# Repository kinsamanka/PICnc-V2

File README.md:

PICnc-V2
========

PICnc V2 is a PIC32 based hardware step generator board that is designed for MachineKit

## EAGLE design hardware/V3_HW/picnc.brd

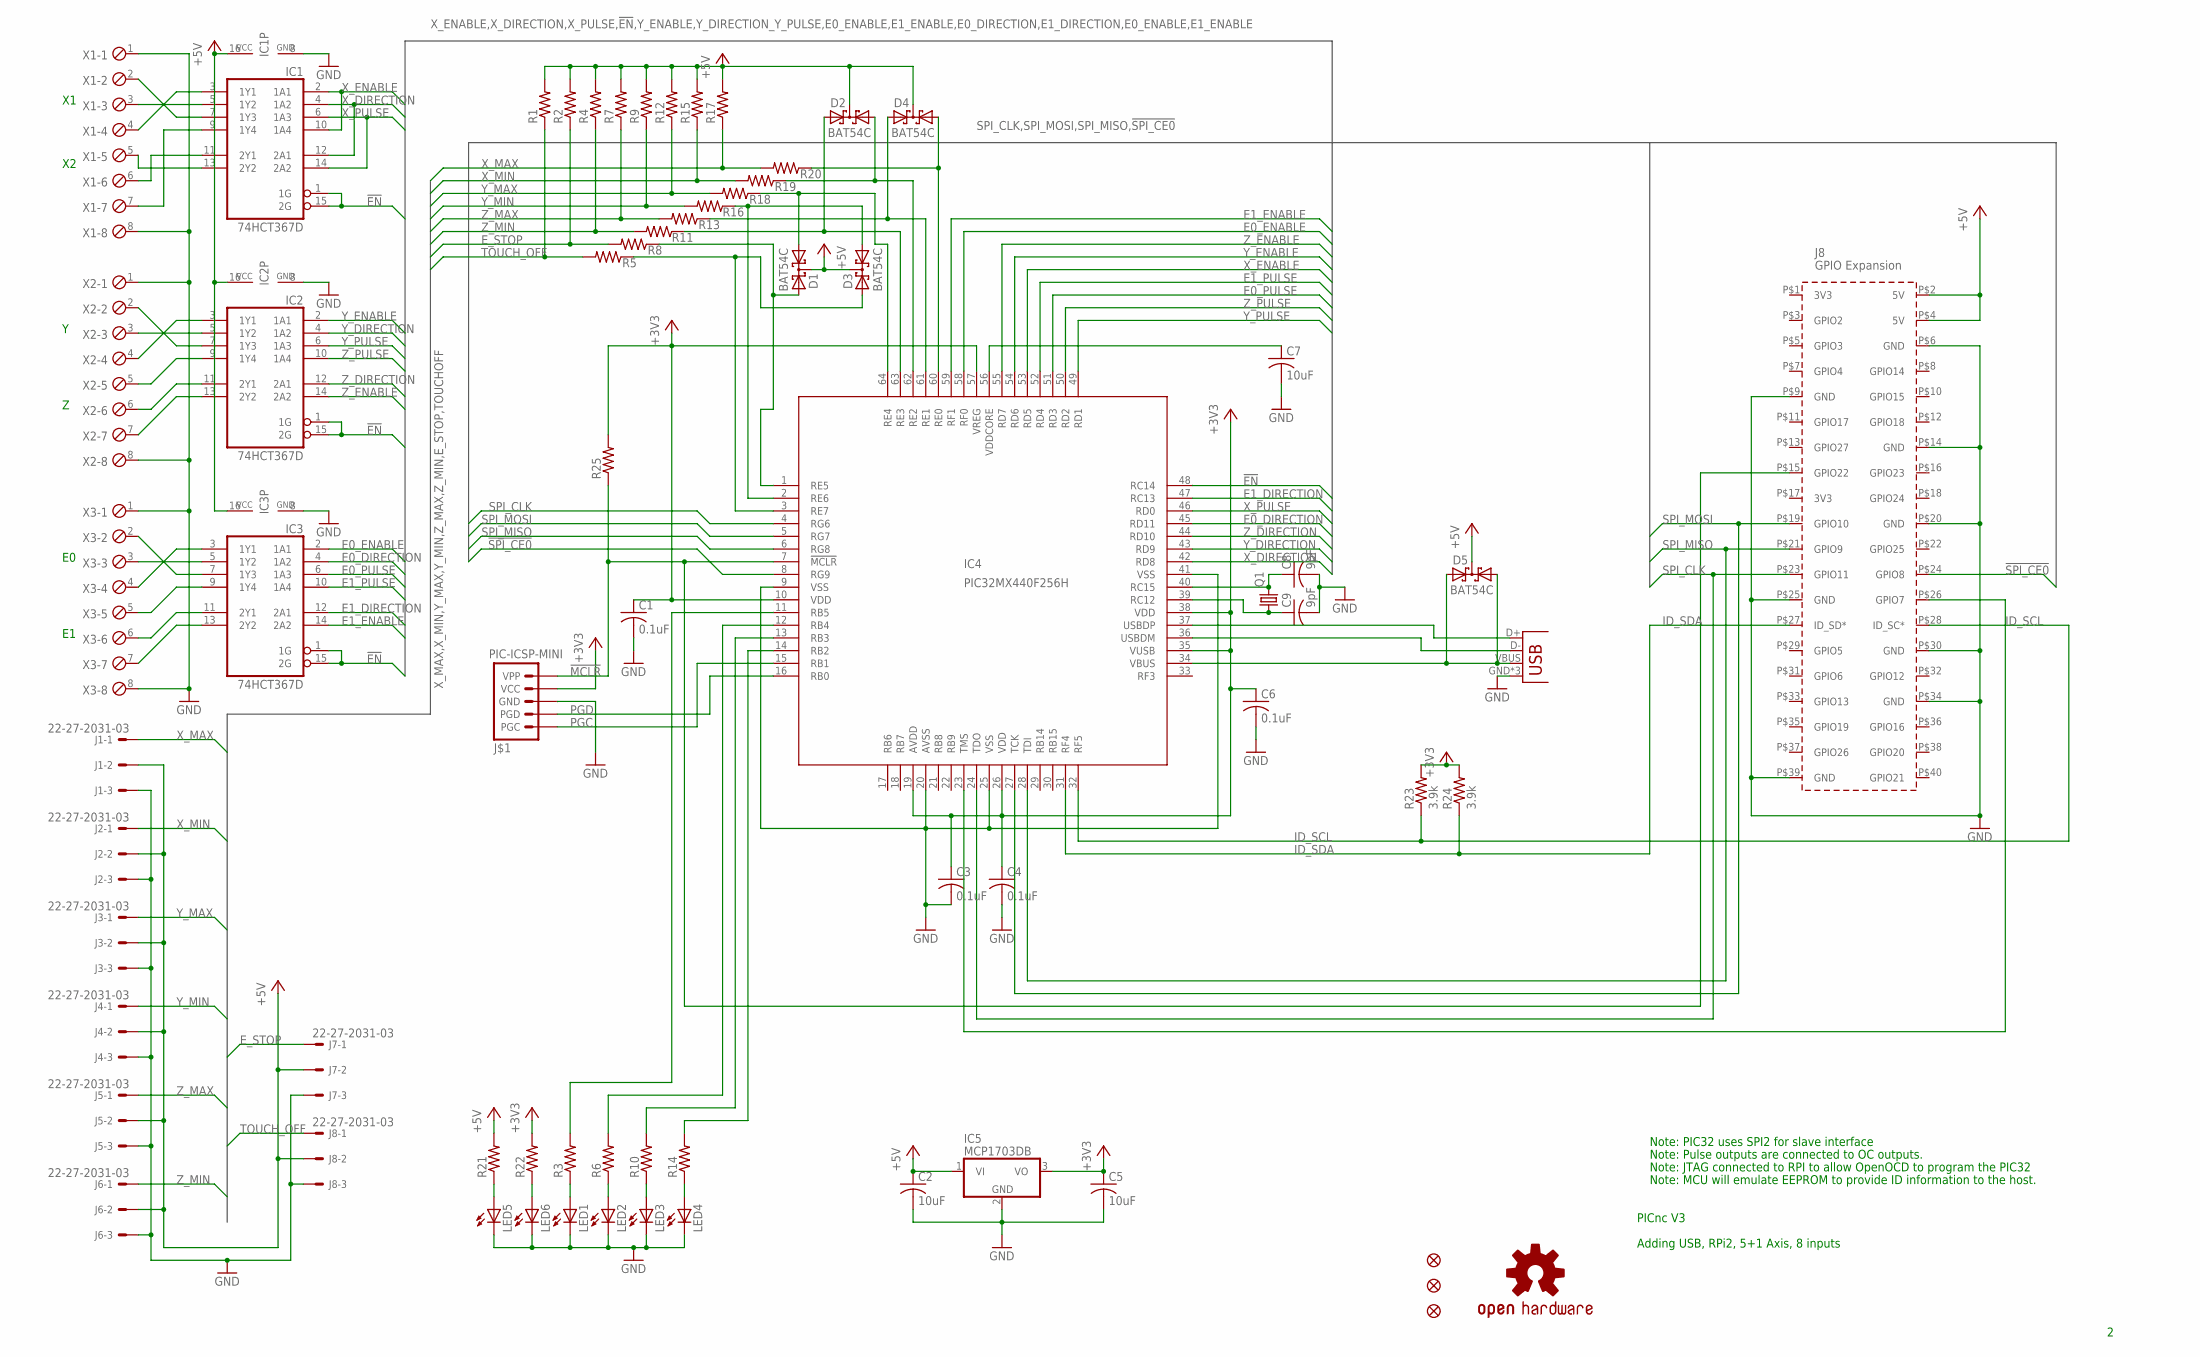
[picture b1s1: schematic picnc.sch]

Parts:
C1, C3, C4, C6: 0.1uF; C0603
C2, C5, C7: 10uF; C1206
C8, C9: 9pF; C0603
D1, D2, D3, D4, D5: BAT54C; SOT23
FID1, FID2, FID3: FIDUCIAL1.5X3; FIDUCIAL-1.5X3
IC1, IC2, IC3: 74HCT367D; SO16
IC4: PIC32MX440F256H; TQFP64-10X10
IC5: MCP1703DB; SOT223
J1, J2, J3, J4, J5, J6, J7, J8: 22-27-2031-03; 6410-03
J9: RPI2_HAT
J$1: PIC-ICSP-MINI
JP1: USB-MICROB
LED1, LED2, LED3, LED4, LED5, LED6: LEDCHIP-LED0603; CHIP-LED0603
LOGO1: OSHW-LOGOS; OSHW-LOGO-S
Q1: CTS406C35D08M00000; CTS406
R1, R2, R3, R4, R5, R6, R7, R8, R9, R10, R11, R12, R13, R14, R15, R16, R17, R18, R19, R20, R21, R22, R25: R-US_R0603; R0603
R23, R24: 3.9k; R0603
X1, X2, X3: MPT8; 8POL254

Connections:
!EN: IC1.1 (1G), IC1.15 (2G), IC2.1 (1G), IC2.15 (2G), IC3.1 (1G), IC3.15 (2G), IC4.48 (RC14)
!MCLR: IC4.7 (!MCLR), J9.P$15 (GPIO22), J$1.1 (VPP), R25.1
!SPI_CE0: J9.P$24 (GPIO8)
+3V3: C1.1, C3.1, C4.1, C5.1, C6.1, IC4.10 (VDD), IC4.19 (AVDD), IC4.26 (VDD), IC4.35 (VUSB), IC4.38 (VDD), IC4.57 (VREG), IC5.3 (VO), J$1.2 (VCC), R22.2, R23.2, R24.2, R25.2
+5V: C2.1, D1.3 (CC), D2.3 (CC), D3.3 (CC), D4.3 (CC), D5.3 (CC), IC1.16 (VCC), IC2.16 (VCC), IC3.16 (VCC), IC5.1 (VI), J1.2, J2.2, J3.2, J4.2, J5.2, J6.2, J7.2, J8.2, J9.P$2 (5V), J9.P$4 (5V), R1.2, R2.2, R4.2, R7.2, R9.2, R12.2, R15.2, R17.2, R21.2
D_N: IC4.36 (USBDM), JP1.D-
D_P: IC4.37 (USBDP), JP1.D+
E0_DIRECTION: IC3.4 (1A2), IC4.45 (RD11)
E0_ENABLE: IC3.2 (1A1), IC4.58 (RF0)
E0_PULSE: IC3.6 (1A3), IC4.51 (RD3)
E1_DIRECTION: IC3.12 (2A1), IC4.47 (RC13)
E1_ENABLE: IC3.14 (2A2), IC4.59 (RF1)
E1_PULSE: IC3.10 (1A4), IC4.52 (RD4)
E_STOP: J7.1, R2.1, R8.2
GND: C1.2, C2.2, C3.2, C4.2, C5.2, C6.2, C7.2, C8.2, C9.2, IC1.8 (GND), IC2.8 (GND), IC3.8 (GND), IC4.9 (VSS), IC4.20 (AVSS), IC4.25 (VSS), IC4.41 (VSS), IC5.2 (GND), J1.3, J2.3, J3.3, J4.3, J5.3, J6.3, J7.3, J8.3, J9.P$6 (GND), J9.P$9 (GND), J9.P$14 (GND), J9.P$20 (GND), J9.P$25 (GND), J9.P$30 (GND), J9.P$34 (GND), J9.P$39 (GND), J$1.3 (GND), JP1.GND, JP1.MT1 (GND), JP1.MT2 (GND), LED1.C, LED2.C, LED3.C, LED4.C, LED5.C, LED6.C, X1.1, X1.8, X2.1, X2.8, X3.1, X3.8
ID_SCL: IC4.32 (RF5), J9.P$28 (ID_SC*), R23.1
ID_SDA: IC4.31 (RF4), J9.P$27 (ID_SD*), R24.1
unnamed: IC1.7 (1Y3), X1.2
unnamed: IC1.3 (1Y1), X1.4
unnamed: IC1.5 (1Y2), X1.3
unnamed: IC1.9 (1Y4), X1.7
unnamed: IC1.11 (2Y1), X1.6
unnamed: IC1.13 (2Y2), X1.5
unnamed: C8.1, IC4.40 (RC15), Q1.3 (2)
unnamed: IC2.5 (1Y2), X2.3
unnamed: C7.1, IC4.56 (VDDCORE)
unnamed: IC2.3 (1Y1), X2.4
unnamed: IC2.7 (1Y3), X2.2
unnamed: IC2.9 (1Y4), X2.5
unnamed: IC2.11 (2Y1), X2.6
unnamed: IC2.13 (2Y2), X2.7
unnamed: IC3.7 (1Y3), X3.2
unnamed: IC3.5 (1Y2), X3.3
unnamed: IC3.3 (1Y1), X3.4
unnamed: IC3.9 (1Y4), X3.5
unnamed: IC3.11 (2Y1), X3.6
unnamed: IC3.13 (2Y2), X3.7
unnamed: C9.1, IC4.39 (RC12), Q1.1
unnamed: LED1.A, R3.1
unnamed: LED2.A, R6.1
unnamed: LED3.A, R10.1
unnamed: LED4.A, R14.1
unnamed: D3.2 (A2), IC4.3 (RE7), R5.1
unnamed: IC4.14 (RB2), R14.2
unnamed: IC4.13 (RB3), R10.2
unnamed: IC4.12 (RB4), R6.2
unnamed: IC4.11 (RB5), R3.2
unnamed: D4.1 (A1), IC4.60 (RE0), R20.1
unnamed: D2.1 (A1), IC4.62 (RE2), R19.1
unnamed: D5.1 (A1), D5.2 (A2), IC4.34 (VBUS), JP1.VBUS
unnamed: D1.1 (A1), IC4.64 (RE4), R18.1
unnamed: D4.2 (A2), IC4.61 (RE1), R13.1
unnamed: D2.2 (A2), IC4.63 (RE3), R11.1
unnamed: D1.2 (A2), IC4.1 (RE5), R8.1
unnamed: D3.1 (A1), IC4.2 (RE6), R16.1
unnamed: IC4.23 (TMS), J9.P$26 (GPIO7)
unnamed: LED5.A, R21.1
unnamed: LED6.A, R22.1
PGC: IC4.15 (RB1), J$1.5 (PGC)
PGD: IC4.16 (RB0), J$1.4 (PGD)
SPI_CLK: IC4.4 (RG6), IC4.24 (TDO), J9.P$23 (GPIO11)
SPI_MISO: IC4.6 (RG8), IC4.28 (TDI), J9.P$21 (GPIO9)
SPI_MOSI: IC4.5 (RG7), IC4.27 (TCK), J9.P$19 (GPIO10)
TOUCH_OFF: J8.1, R1.1, R5.2
X_DIRECTION: IC1.4 (1A2), IC1.12 (2A1), IC4.42 (RD8)
X_ENABLE: IC1.2 (1A1), IC1.10 (1A4), IC4.53 (RD5)
X_MAX: J1.1, R17.1, R20.2
X_MIN: J2.1, R15.1, R19.2
X_PULSE: IC1.6 (1A3), IC1.14 (2A2), IC4.46 (RD0)
Y_DIRECTION: IC2.4 (1A2), IC4.43 (RD9)
Y_ENABLE: IC2.2 (1A1), IC4.54 (RD6)
Y_MAX: J3.1, R12.1, R18.2
Y_MIN: J4.1, R9.1, R16.2
Y_PULSE: IC2.6 (1A3), IC4.49 (RD1)
Z_DIRECTION: IC2.12 (2A1), IC4.44 (RD10)
Z_ENABLE: IC2.14 (2A2), IC4.55 (RD7)
Z_MAX: J5.1, R7.1, R13.2
Z_MIN: J6.1, R4.1, R11.2
Z_PULSE: IC2.10 (1A4), IC4.50 (RD2)

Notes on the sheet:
Note: MCU will emulate EEPROM to provide ID information to the host.
Note: Pulse outputs are connected to OC outputs.
Note: JTAG connected to RPI to allow OpenOCD to program the PIC32
Note: PIC32 uses SPI2 for slave interface
PICnc V3
Adding USB, RPi2, 5+1 Axis, 8 inputs

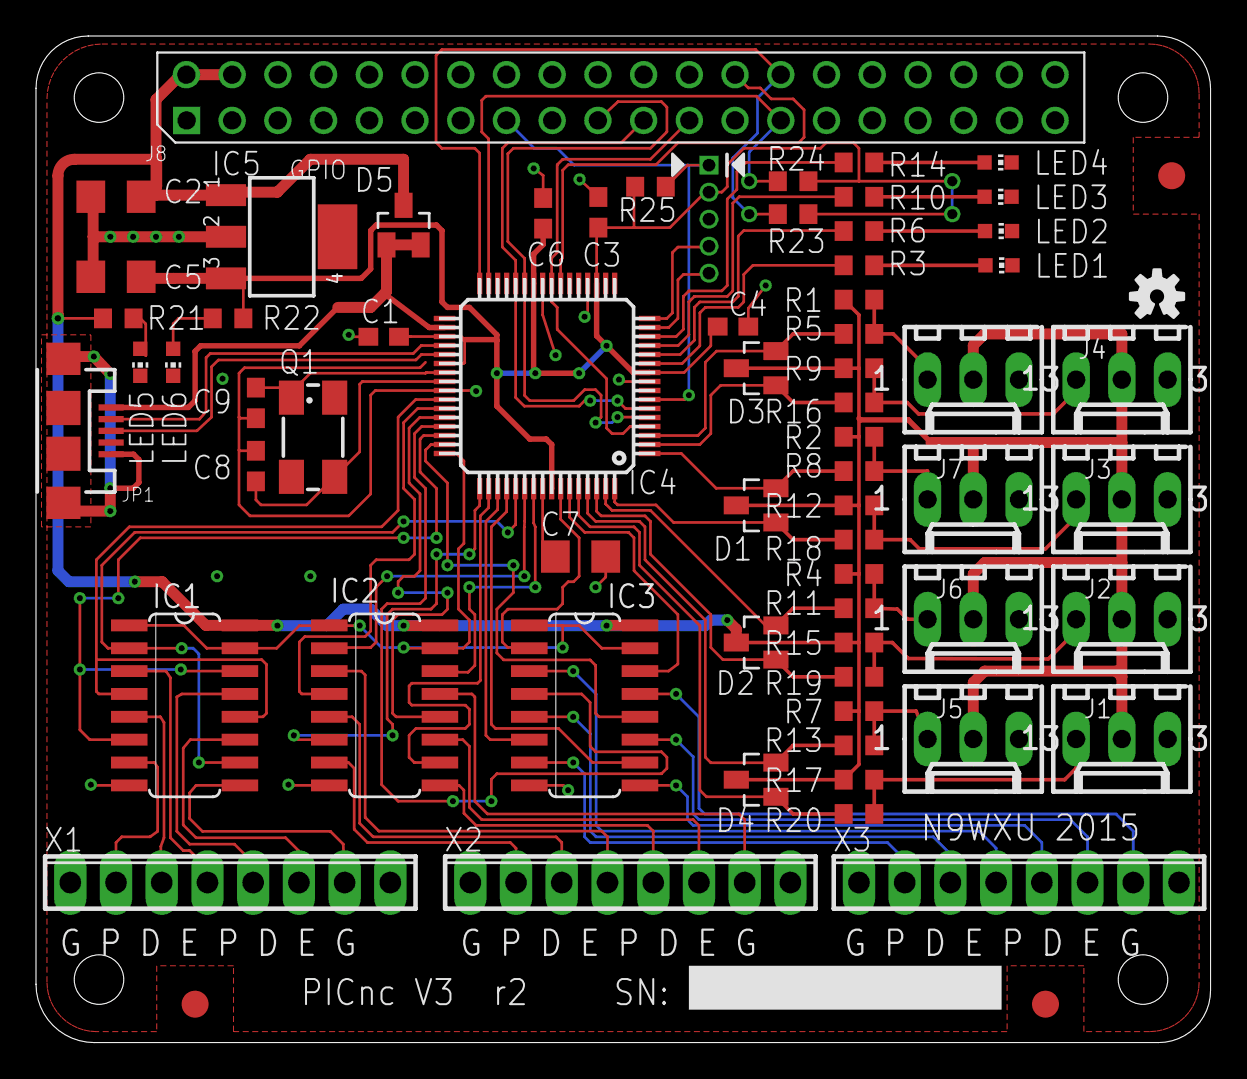
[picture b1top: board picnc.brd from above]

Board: 2 copper layers, 65.3 x 55.9 mm, 69 parts (0 on the bottom side), 78 nets.

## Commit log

2014-06-03 hardware initial commit
2014-06-07 added board outline
2014-08-03 Create gh-pages branch via GitHub
2014-08-15 initial commit for HAL driver and firmware
2014-10-30 fixed int32_t errors for the latest MPIDE compiler
2014-11-08 removed overclocking
2014-11-08 enabled PWM
2014-11-08 refactored HAL driver
2014-11-09 added RPi platform checks
2014-11-27 HAL/picnc.c: fixed param direction
2015-04-08 Changed SPI mode to accommodate Odroid C1 SPI bug
2015-04-08 fixed wrong SYS_FREQ
2015-04-08 changed SPI mode to make it compatible with Odroid C1
2015-04-10 Odroid C1 support
2015-04-10 added RPi2 support
2015-04-10 updated hex file
2015-04-13 fixed SPI polarity
2015-04-14 Added support for Odroid C1
2015-04-14 fixed incorrect scale parameter
2015-12-18 PIC32MX4 Modifications & MPLAB Project
    Improved performance and ported to the MX4.
2015-12-18 Actual changes to main and stepgen
    Previous update did not include the important changes.
2015-12-18 Added the V3 HW files
    These files are a modification from the OSHPARK build.
    OSHPARK revision needs MCLR & I2C pullup resistors. I2C is optional for
    now.
2015-12-19 X1_ENABLE is not connected on the Hardware
    PWM's now mapped to the step channels.
    Enables are now mapped as the step channels
    E1_Direction is now the master stepper driver enable.
    X_STEP is still the step because X_ENABLE is defective.
    OC2-4 are used for PWM OC1 is not used.
2015-12-20 200khz update
    refactored to go back to a single call to stepgen.
    added a macro to make the step generation DRY.
    reduced the step accumulator to 65536 (not really sure if this is a good
    idea)
    increased the core timer rate to 200khz (52% CPU for step generation on
    4 Axis)
2015-12-20 restored original step algorithm.
    I restored the original step algorithm sans stepwidth adjustment. It is
    still operating at 200khz.
2015-12-24 FIFO output attempt
    attempted to speed up the ISR by generating the step pattern in a FIFO
2015-12-24 put it back to 200khz ISR generated steps
    It can't produce more than 1 step ahead reliably so the ISR runs dry
    when operating with a FIFO.

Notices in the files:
parts and their libraries:
SparkFun-Connectors: Licensing: CC v3.0 Share-Alike You are welcome to use this library for commercial purposes.
